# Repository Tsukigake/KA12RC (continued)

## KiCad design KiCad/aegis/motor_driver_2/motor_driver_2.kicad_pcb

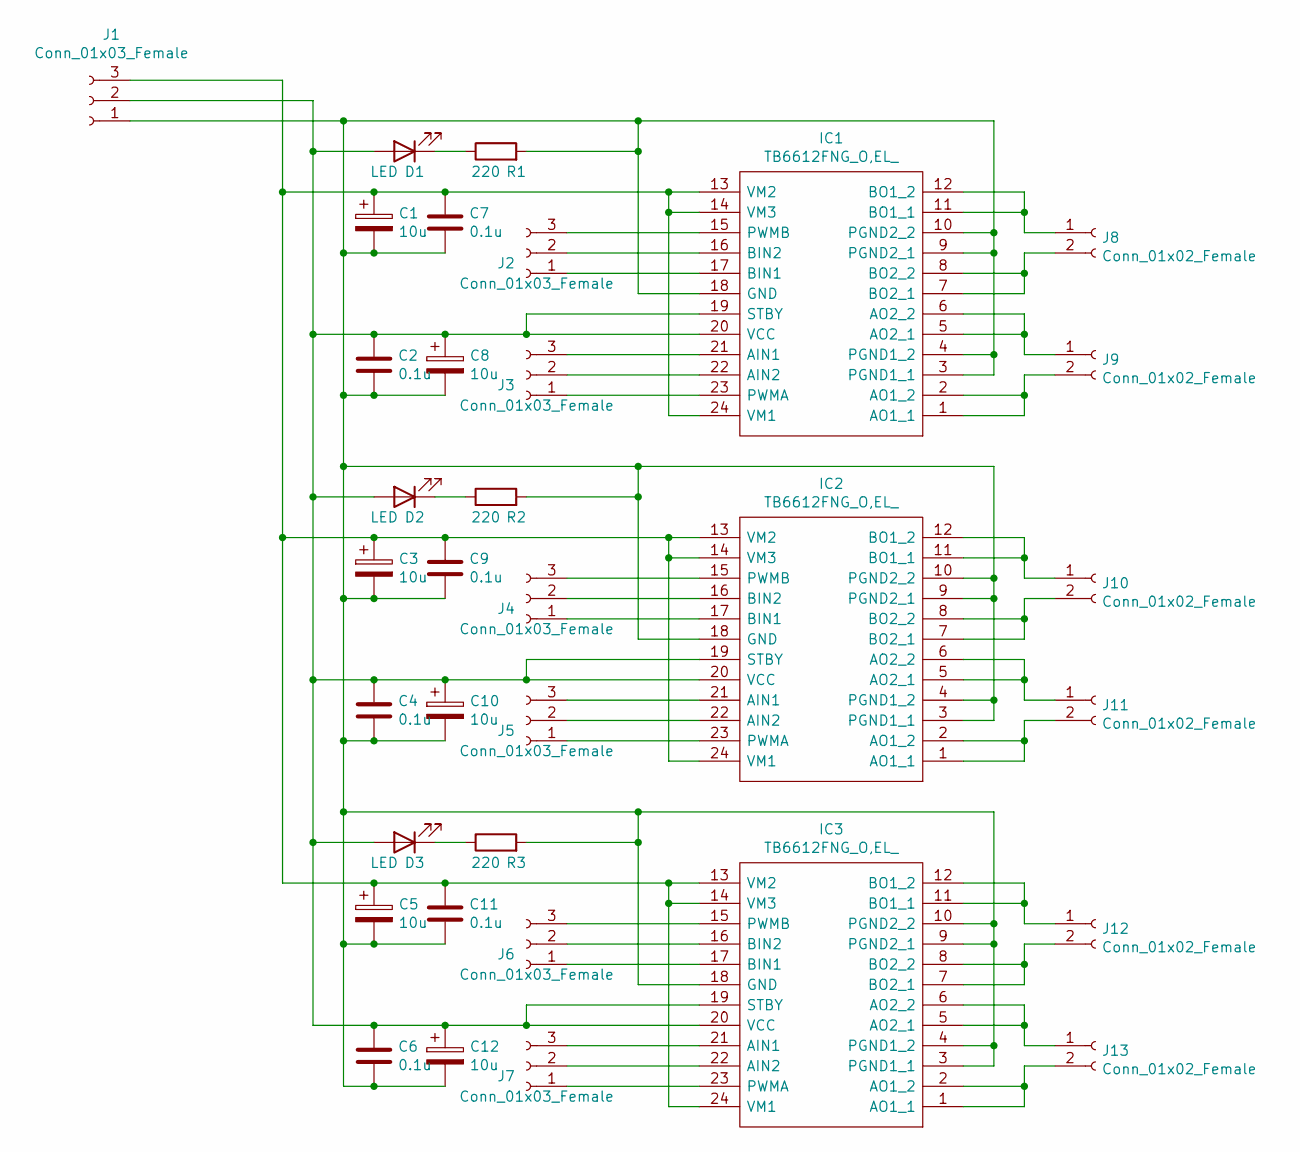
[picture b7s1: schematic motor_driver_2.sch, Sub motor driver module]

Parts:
C1, C3, C5, C8, C10, C12: 10u; CAPAE430X730N
C2, C4, C6, C7, C9, C11: 0.1u; CAPC1608X90N
D1, D2, D3: LED; OSXX0603C1E
IC1, IC2, IC3: TB6612FNG_O,EL_; SOP65P760X160-24N; Manufacturer_Part_Number TB6612FNG(O,EL)
J1, J2, J3, J4, J5, J6, J7: Conn_01x03_Female; PinHeader_1x03_P2.54mm_Vertical
J8, J9, J10, J11, J12, J13: Conn_01x02_Female; PinHeader_1x02_P2.54mm_Vertical
R1, R2, R3: 220; RESC3216X70N

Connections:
unnamed: C1.1, C3.1, C5.1, C7.1, C9.1, C11.1, IC1.13 (VM2), IC1.14 (VM3), IC1.24 (VM1), IC2.13 (VM2), IC2.14 (VM3), IC2.24 (VM1), IC3.13 (VM2), IC3.14 (VM3), IC3.24 (VM1), J1.3
unnamed: C1.2, C2.2, C3.2, C4.2, C5.2, C6.2, C7.2, C8.2, C9.2, C10.2, C11.2, C12.2, IC1.3 (PGND1_1), IC1.4 (PGND1_2), IC1.9 (PGND2_1), IC1.10 (PGND2_2), IC1.18 (GND), IC2.3 (PGND1_1), IC2.4 (PGND1_2), IC2.9 (PGND2_1), IC2.10 (PGND2_2), IC2.18 (GND), IC3.3 (PGND1_1), IC3.4 (PGND1_2), IC3.9 (PGND2_1), IC3.10 (PGND2_2), IC3.18 (GND), J1.1, R1.2, R2.2, R3.2
unnamed: C2.1, C4.1, C6.1, C8.1, C10.1, C12.1, D1.2 (A), D2.2 (A), D3.2 (A), IC1.19 (STBY), IC1.20 (VCC), IC2.19 (STBY), IC2.20 (VCC), IC3.19 (STBY), IC3.20 (VCC), J1.2
unnamed: D1.1 (K), R1.1
unnamed: D2.1 (K), R2.1
unnamed: D3.1 (K), R3.1
unnamed: IC1.1 (AO1_1), IC1.2 (AO1_2), J9.2
unnamed: IC1.5 (AO2_1), IC1.6 (AO2_2), J9.1
unnamed: IC1.7 (BO2_1), IC1.8 (BO2_2), J8.2
unnamed: IC1.11 (BO1_1), IC1.12 (BO1_2), J8.1
unnamed: IC1.15 (PWMB), J2.3
unnamed: IC1.16 (BIN2), J2.2
unnamed: IC1.17 (BIN1), J2.1
unnamed: IC1.21 (AIN1), J3.3
unnamed: IC1.22 (AIN2), J3.2
unnamed: IC1.23 (PWMA), J3.1
unnamed: IC2.1 (AO1_1), IC2.2 (AO1_2), J11.2
unnamed: IC2.5 (AO2_1), IC2.6 (AO2_2), J11.1
unnamed: IC2.7 (BO2_1), IC2.8 (BO2_2), J10.2
unnamed: IC2.11 (BO1_1), IC2.12 (BO1_2), J10.1
unnamed: IC2.15 (PWMB), J4.3
unnamed: IC2.16 (BIN2), J4.2
unnamed: IC2.17 (BIN1), J4.1
unnamed: IC2.21 (AIN1), J5.3
unnamed: IC2.22 (AIN2), J5.2
unnamed: IC2.23 (PWMA), J5.1
unnamed: IC3.1 (AO1_1), IC3.2 (AO1_2), J13.2
unnamed: IC3.5 (AO2_1), IC3.6 (AO2_2), J13.1
unnamed: IC3.7 (BO2_1), IC3.8 (BO2_2), J12.2
unnamed: IC3.11 (BO1_1), IC3.12 (BO1_2), J12.1
unnamed: IC3.15 (PWMB), J6.3
unnamed: IC3.16 (BIN2), J6.2
unnamed: IC3.17 (BIN1), J6.1
unnamed: IC3.21 (AIN1), J7.3
unnamed: IC3.22 (AIN2), J7.2
unnamed: IC3.23 (PWMA), J7.1

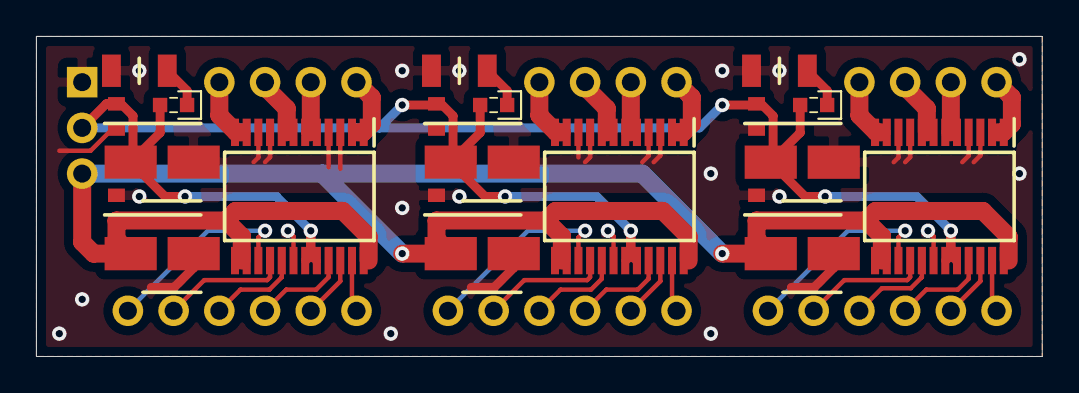
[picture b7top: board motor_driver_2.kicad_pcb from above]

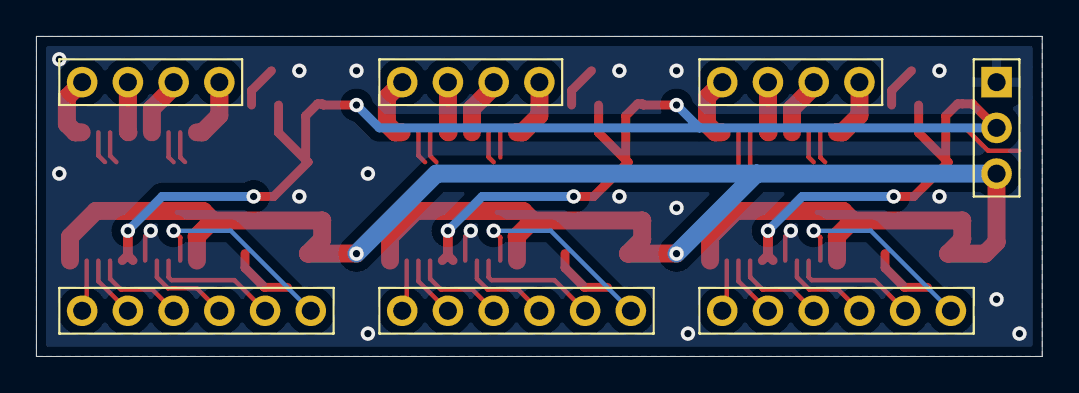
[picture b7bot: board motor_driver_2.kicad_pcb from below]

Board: 2 copper layers, 55.9 x 17.8 mm, 34 parts (13 on the bottom side), 36 nets.
